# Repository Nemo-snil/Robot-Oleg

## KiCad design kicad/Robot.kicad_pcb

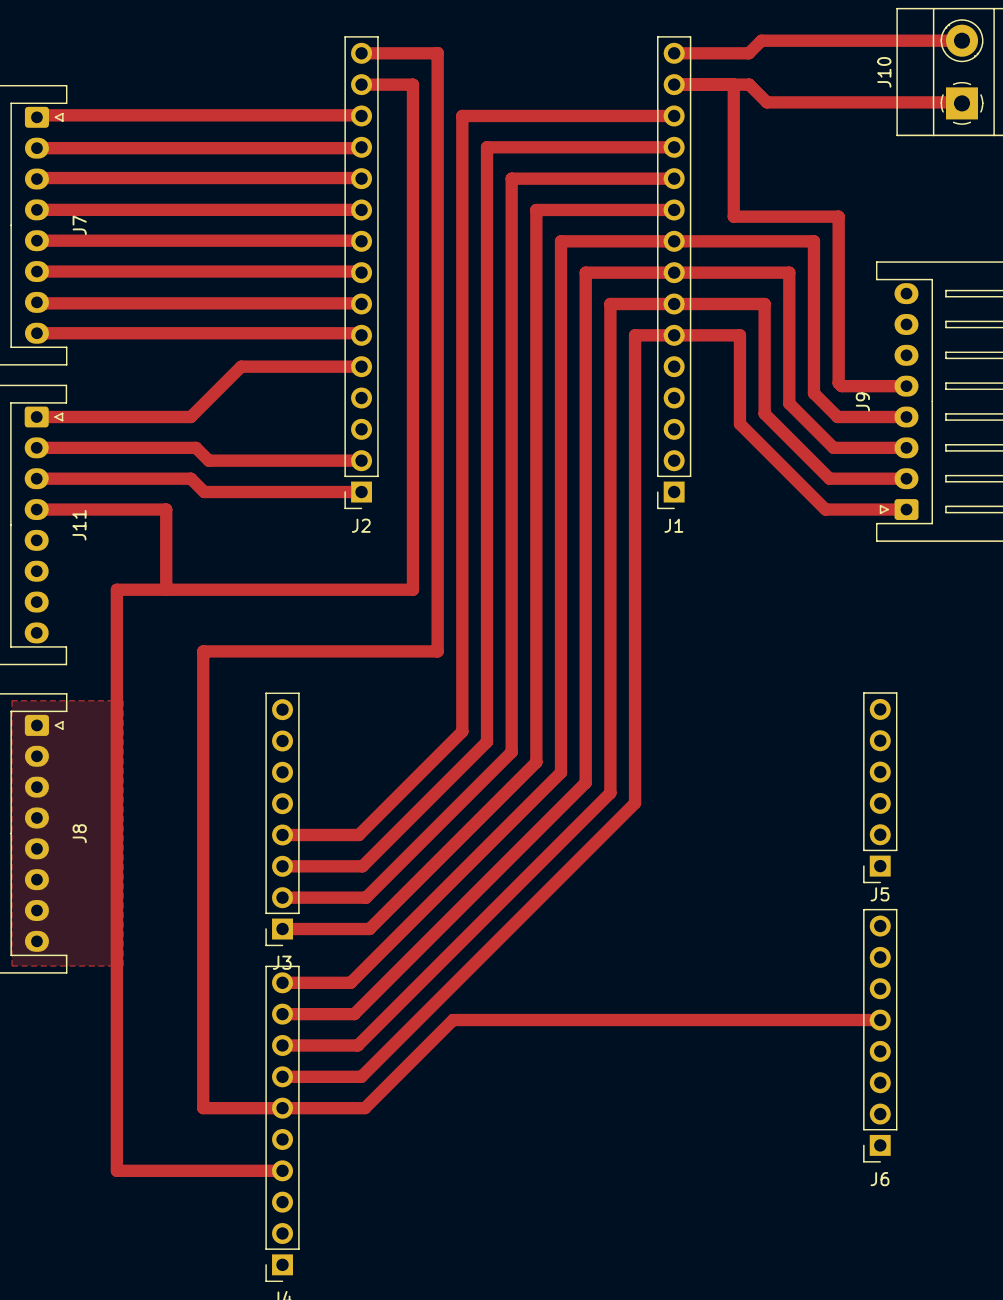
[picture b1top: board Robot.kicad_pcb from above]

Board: 2 copper layers, 11 parts (0 on the bottom side), 22 nets.

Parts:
J1: ESP32 1; PinSocket_1x15_P2.54mm_Vertical
J2: ESP32 2; PinSocket_1x15_P2.54mm_Vertical
J3: Conn_01x08_Socket; PinSocket_1x08_P2.54mm_Vertical
J4: DIGITAL PWM(~); PinSocket_1x10_P2.54mm_Vertical
J5: ANALOG IN; PinSocket_1x06_P2.54mm_Vertical
J6: POWER; PinSocket_1x08_P2.54mm_Vertical
J7: Limit switch; JST_XH_S8B-XH-A_1x08_P2.50mm_Horizontal
J8: Limit switch GND; JST_XH_S8B-XH-A_1x08_P2.50mm_Horizontal
J9: BTS7960; JST_XH_S8B-XH-A_1x08_P2.50mm_Horizontal
J10: Power; TerminalBlock_Phoenix_MKDS-1,5-2-5.08_1x02_P5.08mm_Horizont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
J11: I2C; JST_XH_S8B-XH-A_1x08_P2.50mm_Horizontal

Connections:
+3.3V: J2.15, J4.6, J6.5
+12V: J1.15, J10.2
D2: J2.12, J7.2
D4: J2.11, J7.3
D5: J2.8, J7.6
D12: J1.12, J3.3
D13: J1.13, J3.4
D14: J1.11, J3.2
D15: J2.13, J7.1
D18: J2.7, J7.7
D19: J2.6, J7.8
D23: J2.1, J11.3
D25: J1.8, J4.9, J9.3
D26: J1.9, J4.10, J9.4
D27: J1.10, J3.1
D32: J1.6, J4.7, J9.1
D33: J1.7, J4.8, J9.2
GND: J1.14, J2.14, J4.4, J8.1, J8.2, J8.3, J8.4, J8.5, J8.6, J8.7, J8.8, J9.5, J10.1, J11.4
RX2: J2.10, J7.4
SCL: J2.2, J11.2
SDA: J2.5, J11.1
TX2: J2.9, J7.5

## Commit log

2025-02-16 init
2025-02-16 Уменьшена скорость подъема и опускание механизма
2025-02-17 Изменен порт
2025-02-17 Изменения имени папки
2025-02-17 Сервис не ожидает окончания поднятия механизма
2025-02-17 Сервис не ожидает сброса энкодеров
2025-02-17 Изменен baud rate
2025-02-17 Увелиен приоритет сервиса сброса энкодеров
2025-02-17 fix navigation
2025-02-17 Уменьшение скорости при управлении джойстиком
2025-02-17 Смещение камеры
2025-02-17 Увеличение стэка
2025-02-17 Устранена утечка памяти на esp32
2025-02-17 Фикс езды по аруко метке
2025-02-17 Новая карта
2025-02-17 Изменена презентация
